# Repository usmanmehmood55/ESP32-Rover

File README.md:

# ESP32 based UGV
Made using PlatformIO and being tested on a custom PCB for my final
year project: 3D Mapping using Stereo Vision. This board, along with
its firmware are simply handle two DC motors, their encoders and two servo motors. 
The motors are driven by DRV8840 chip, for which, a simple and easy to use library 
has been written and included.

MQTT added on June 5th. Receives 10-character commands from Nvidia Jetson TX2 
to operate motors and return distance traveled

Still working on distance calculations, had *some* progress with it, which is included in the latest commit

Contains main cpp file in src folder and DRV8840.h in include folder

Also might contain gluten.

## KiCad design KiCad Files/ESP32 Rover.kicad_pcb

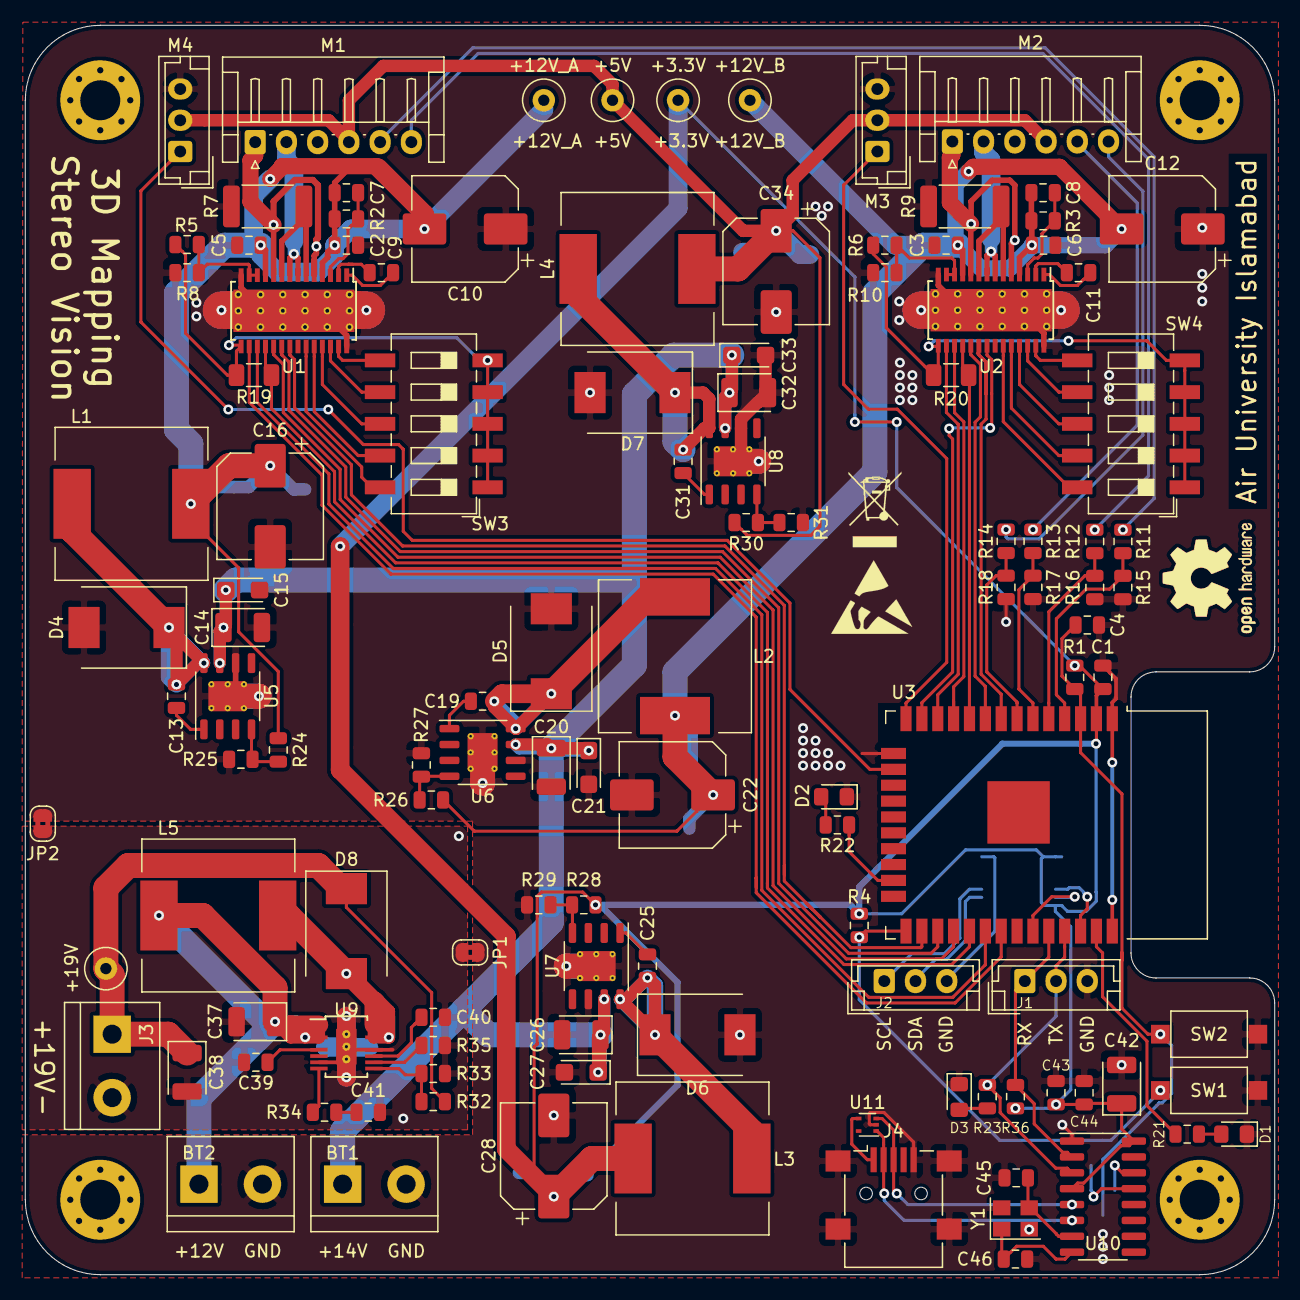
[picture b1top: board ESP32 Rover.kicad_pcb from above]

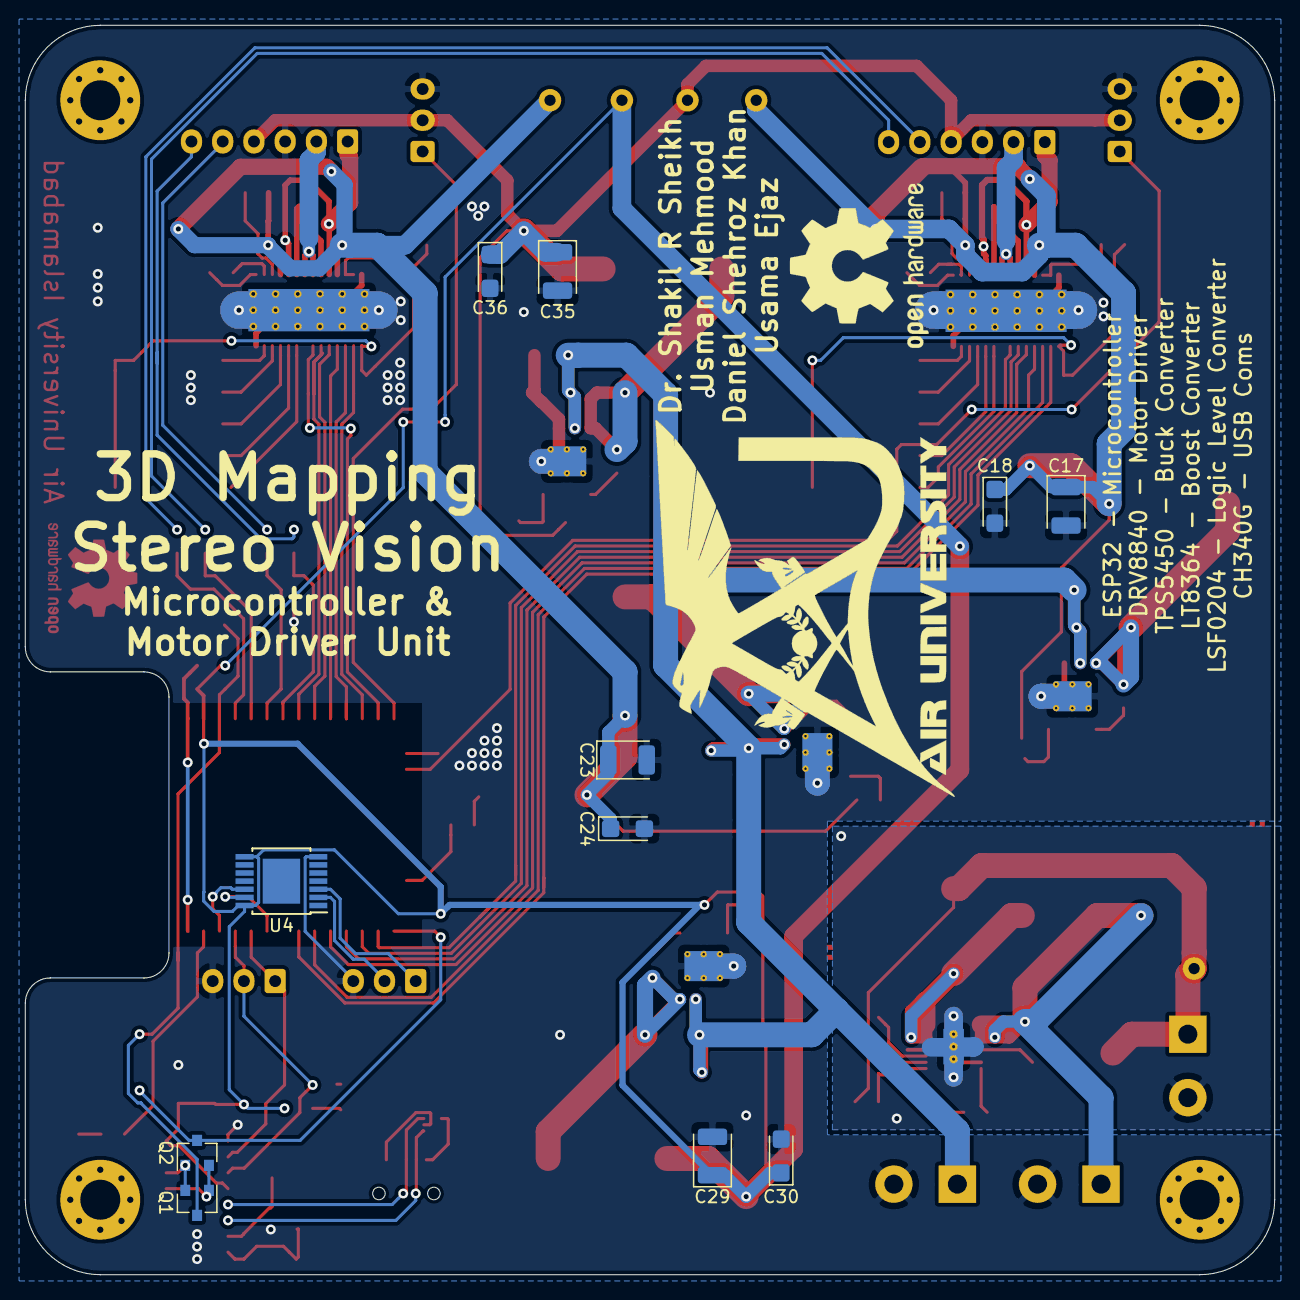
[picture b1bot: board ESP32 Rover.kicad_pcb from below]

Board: 2 copper layers, 100.0 x 100.0 mm, 138 parts (11 on the bottom side), 96 nets.

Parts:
BIN: BIN; WEEE-Logo_4.2x6mm_SilkScreen
BT1: 14.8V; TerminalBlock_bornier-2_P5.08mm
BT2: 11.1V; TerminalBlock_bornier-2_P5.08mm
C1, C39: 1uF; C_0805_2012Metric
C2, C3, C5, C6, C7, C8: 0.1uF; C_0805_2012Metric
C4, C9, C11, C13, C19, C25, C31, C43: 100nF; C_0805_2012Metric
C10, C12: 100uF; CP_Elec_8x10
C14, C17, C20, C23, C26, C29, C32, C35, C37, C38, C42: 4.7uF; CP_EIA-3528-15_AVX-H
C15, C18, C21, C24, C27, C30, C33, C36: 220nF; CP_EIA-3216-18_Kemet-A
C16, C22, C28, C34: 330uF; CP_Elec_8x10
C40, C44: 10nF; C_0805_2012Metric
C41: 2.2nF; C_0805_2012Metric
C45, C46: 22pF; C_0805_2012Metric
D1, D2, D3: LED; LED_0805_2012Metric_Pad1.15x1.40mm_HandSolder
D4, D5, D6, D7, D8: 5A; D_SMC
ESD: ESD; ESD-Logo_6.6x6mm_SilkScreen
H1, H2, H3, H4: MH; MountingHole_3.2mm_M3_Pad_Via
J1: UART; JST_EH_B3B-EH-A_1x03_P2.50mm_Vertical
J2: i2c_jetson; JST_EH_B3B-EH-A_1x03_P2.50mm_Vertical
J3: T-Block; TerminalBlock_bornier-2_P5.08mm
J4: USB_B_Mini; USB_Mini-B_Lumberg_2486_01_Horizontal
JP1, JP2: SolderJumper_2_Bridged; SolderJumper-2_P1.3mm_Bridged2Bar_RoundedPad1.0x1.5mm
L1, L2, L3, L4: 15uH; L_Pulse_PA4320
L5: 2.4uH; L_Pulse_PA4320
M1, M2: PL37D; JST_EH_S6B-EH_1x06_P2.50mm_Horizontal
M3, M4: Servo; JST_EH_B3B-EH-A_1x03_P2.50mm_Vertical
OSHW: OSHW; OSHW-Logo2_9.8x8mm_SilkScreen
OSHW#2: OSHW; OSHW-Logo2_9.8x8mm_Copper
Q1, Q2: BSS138; SOT-23
R1, R4, R5, R6, R24, R25, R26, R27, R28, R29, R30, R31: 10K; R_0805_2012Metric
R2, R3: 1M; R_0805_2012Metric
R7, R9: 0.1R; R_2512_6332Metric
R8, R10: 31K; R_0805_2012Metric
R11, R12, R13, R14: 1K; R_0805_2012Metric
R15, R16, R17, R18: 2K; R_0805_2012Metric
R19, R20: 10K; R_1206_3216Metric
R21, R22, R23: 83; R_0805_2012Metric
R32: 10k; R_0805_2012Metric
R33: 100k; R_0805_2012Metric
R34: 36.5k; R_0805_2012Metric
R35: 20k; R_0805_2012Metric
R36: 4.7K; R_0805_2012Metric
SW1: BOOT/FLASH; SW_SPST_CK_RS282G05A3
SW2: RESET; SW_SPST_CK_RS282G05A3
SW3, SW4: iChop; SW_DIP_SPSTx05_Slide_6.7x14.26mm_W8.61mm_P2.54mm_LowProfile
TP1: +12V_A; TestPoint_Loop_D2.60mm_Drill0.9mm_Beaded
TP2: +12V_B; TestPoint_Loop_D2.60mm_Drill0.9mm_Beaded
TP3: +3.3V; TestPoint_Loop_D2.60mm_Drill0.9mm_Beaded
TP4: +5V; TestPoint_Loop_D2.60mm_Drill0.9mm_Beaded
TP5: +19V; TestPoint_Loop_D2.60mm_Drill0.9mm_Beaded
U1, U2: DRV8840; HTSSOP-28-1EP_4.4x9.7mm_P0.65mm_EP3.4x9.5mm_Mask2.4x6.17mm_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
U3: ESP32-WROOM-32D; ESP32-WROOM-32
U4: LSF0204; TSSOP-14-1EP_4.4x5mm_P0.65mm
U5, U6, U7, U8: TPS5450; HSOP-8-1EP_3.9x4.9mm_P1.27mm_EP2.41x3.1mm_ThermalVias
U9: LT8364; MSOP-12-16-1EP_3x4mm_P0.5mm_EP1.65x2.85mm_ThermalVias
U10: CH340G; SOIC-16_3.9x9.9mm_P1.27mm
U11: ESDA6V8AV5; SOT-553
Y1: 12MHz; Crystal_SMD_3225-4Pin_3.2x2.5mm

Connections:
3P3_1: R5.1, R19.1, SW3.1, SW3.2, SW3.3, SW3.4, SW3.5, U1.15
3P3_2: R6.1, R20.1, SW4.1, SW4.2, SW4.3, SW4.4, SW4.5, U2.15
+3V3: C1.1, C28.1, C29.1, C30.1, C42.1, C43.1, C44.1, L3.2, R1.1, R4.1, R28.1, R36.1, TP3.1, U3.2, U4.8, U4.14, U10.4, U10.16
+5V: C34.1, C35.1, C36.1, L4.2, M1.4, M2.4, M3.2, M4.2, R30.1, TP4.1
+12V: BT2.1, C37.1, L5.1, U9.1, U9.3
/M1+: M1.1, U1.5, U1.10
/M1-: M1.2, U1.7, U1.8
/M2+: M2.1, U2.5, U2.10
/M2-: M2.2, U2.7, U2.8
BOOT: Q2.3, R4.2, SW1.1, U3.25
D+: J4.3, U10.5, U11.3
D-: J4.2, U10.6, U11.1
DTR: Q1.1, Q2.2, U10.13
EC1A: R11.2, R15.1, U3.4
EC1B: R12.2, R16.1, U3.5
EC2A: R13.2, R17.1, U3.6
EC2B: R14.2, R18.1, U3.7
EN: C4.1, Q1.3, R1.2, SW2.1, U3.3
ENC1A: M1.5, R11.1
ENC1B: M1.6, R12.1
ENC2A: M2.5, R13.1
ENC2B: M2.6, R14.1
GND: BT1.2, BT2.2, C1.2, C2.1, C3.1, C4.2, C5.1, C6.1, C10.1, C12.1, C14.2, C15.2, C16.2, C17.2, C18.2, C20.2, C21.2, C22.2, C23.2, C24.2, C26.2, C27.2, C28.2, C29.2, C30.2, C32.2, C33.2, C34.2, C35.2, C36.2, C42.2, C43.2, C44.2, C45.2, C46.2, D1.1, D2.1, D3.1, D4.2, D5.2, D6.2, D7.2, J1.3, J2.3, J4.5, J4.6, JP1.1, JP2.1, M1.3, M2.3, M3.3, M4.3, R7.2, R8.2, R9.2, R10.2, R15.2, R16.2, R17.2, R18.2, R25.2, R27.2, R29.2, R31.2, SW1.2, SW2.2, U1.14, U1.28, U1.29, U2.14, U2.28, U2.29, U3.1, U3.15, U3.38, U4.7, U5.6, U5.9, U6.6, U6.9, U7.6, U7.9, U8.6, U8.9, U10.1, U11.2, Y1.2, Y1.4
GNDD: C37.2, C38.2, C39.2, C40.2, C41.2, J3.2, JP1.2, JP2.2, R33.2, R35.1, U9.7, U9.12, U9.17
M1C0: SW3.10, U1.23
M1C1: SW3.9, U1.24
M1C2: SW3.8, U1.25
M1C3: SW3.7, U1.26
M1C4: SW3.6, U1.27
M1DECAY: U1.19, U3.28
M1FAULT: R19.2, U1.18, U3.29
M1PHASE: U1.20, U3.27
M1PWM: U1.21, U3.26
M1RST: U1.16, U3.31
M1SLEEP: U1.17, U3.30
M2C0: SW4.10, U2.23
M2C1: SW4.9, U2.24
M2C2: SW4.8, U2.25
M2C3: SW4.7, U2.26
M2C4: SW4.6, U2.27
M2DECAY: U2.19, U3.9
M2FAULT: R20.2, U2.18, U3.10
M2PHASE: U2.20, U3.8
M2PWM: U2.21, U3.13
M2RST: U2.16, U3.12
M2SLEEP: U2.17, U3.11
unnamed: C7.2, R2.2, U1.3
unnamed: C8.2, R3.2, U2.3
unnamed: C9.1, U1.1
unnamed: C9.2, U1.2
unnamed: C11.1, U2.1
unnamed: C11.2, U2.2
unnamed: C13.1, D4.1, L1.1, U5.8
unnamed: C13.2, U5.1
unnamed: C19.1, D5.1, L2.1, U6.8
unnamed: C19.2, U6.1
unnamed: C25.1, D6.1, L3.1, U7.8
unnamed: C25.2, U7.1
unnamed: C31.1, D7.1, L4.1, U8.8
unnamed: C31.2, U8.1
unnamed: C39.1, U9.5
unnamed: C40.1, U9.11
unnamed: C41.1, R34.2
unnamed: D1.2, R21.2
unnamed: D2.2, R22.2
unnamed: D3.2, R23.2
unnamed: D8.2, L5.2, U9.14, U9.16
unnamed: R5.2, R8.1, U1.12, U1.13
unnamed: R7.1, U1.6, U1.9
unnamed: R9.1, U2.6, U2.9
unnamed: R6.2, R10.1, U2.12, U2.13
unnamed: R32.2, R33.1, U9.9
unnamed: R34.1, U9.8
unnamed: R35.2, U9.10
O1: C45.1, U10.7, Y1.3
O2: C46.1, U10.8, Y1.1
RTS: Q1.2, Q2.1, U10.14
RX: J1.1, R36.2, U3.34, U10.2
SCL: U3.36, U4.12
SCL1: J2.1, U4.3
SDA: U3.33, U4.13
SDA1: J2.2, U4.2
SRV1: M3.1, U3.14
SRV2: M4.1, U3.16
STAT1: R21.1, U3.37
STAT2: R22.1, U3.23
TX: J1.2, R23.1, U3.35, U10.3
VBUS: J4.1, U11.4
VDC: BT1.1, C14.1, C15.1, C20.1, C21.1, C26.1, C27.1, C32.1, C33.1, U5.7, U6.7, U7.7, U8.7
VSNS1: R24.2, R25.1, U5.4
VSNS2: R26.2, R27.1, U6.4
VSNS3: R28.2, R29.1, U7.4
VSNS4: R30.2, R31.1, U8.4
V_SoC: C38.1, D8.1, J3.1, R32.1, TP5.1
vMotor1: C2.2, C5.2, C7.1, C10.2, C16.1, C17.1, C18.1, L1.2, R2.1, R24.1, TP1.1, U1.4, U1.11
vMotor2: C3.2, C6.2, C8.1, C12.2, C22.1, C23.1, C24.1, L2.2, R3.1, R26.1, TP2.1, U2.4, U2.11

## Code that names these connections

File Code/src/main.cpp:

#include <Arduino.h>
#include <DRV8840.h>

// Motor Driver IN
unsigned const char M1RST = 19;
unsigned const char M1PWM = 04;
unsigned const char M1PHASE = 16;
unsigned const char M1SLEEP = 18;
unsigned const char M1DECAY = 17;
unsigned const char M2RST = 27;
unsigned const char M2PWM = 14;
unsigned const char M2PHASE = 32;
unsigned const char M2SLEEP = 26;
unsigned const char M2DECAY = 33;

//Motor Driver OUT
unsigned const char ENCODER_1A = 36;
unsigned const char ENCODER_1B = 39;
unsigned const char ENCODER_2A = 34;
unsigned const char ENCODER_2B = 35;
unsigned const char M1FAULT = 05;
unsigned const char M2FAULT = 25;

// PWM
unsigned const char PWMchannel_0 = 0;
unsigned const char PWMchannel_1 = 1;
unsigned const int freq = 5000;
unsigned const char resolution = 8;

DRV8840 M1(
    M1PWM,
    PWMchannel_0,
    M1PHASE,
    M1DECAY,
    M1SLEEP,
    M1RST,
    ENCODER_1A,
    ENCODER_1B);

DRV8840 M2(
    M2PWM,
    PWMchannel_1,
    M2PHASE,
    M2DECAY,
    M2SLEEP,
    M2RST,
    ENCODER_2A,
    ENCODER_2B);

int distance1 = 0;
int distance2 = 0;

void encoderRead1();
void encoderRead2();

void setup()
{
  Serial.begin(115200);

  pinMode(M1FAULT, INPUT);
  pinMode(M2FAULT, INPUT);
  attachInterrupt(digitalPinToInterrupt(ENCODER_1B), encoderRead1, CHANGE);
  attachInterrupt(digitalPinToInterrupt(ENCODER_2B), encoderRead2, CHANGE);

  // PWM Setup
  ledcSetup(PWMchannel_0, freq, resolution);
  ledcAttachPin(M1PWM, PWMchannel_0);
  ledcSetup(PWMchannel_1, freq, resolution);
  ledcAttachPin(M2PWM, PWMchannel_1);

  M1.getData();
  M2.getData();
  Serial.println();
  Serial.println("Setup Complete!");
}

void loop()
{
  M1.motorForward(255); 
  Serial.print(M1.getDistance());
  Serial.print("    ");
  M2.motorForward(255); 
  Serial.print(M1.getDistance());
  Serial.println();
}

// Use if ISR inside DRV8840.h does not run
void IRAM_ATTR encoderRead1()
{
  M1.encoderRead();
}

void IRAM_ATTR encoderRead2()
{
  M2.encoderRead();
}

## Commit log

2020-03-08 Remove duplicated directory
2020-03-08 Linked to Git
2020-03-08 Files Updated
2020-03-08 Repairs lol
2020-03-08 Readme added
2020-03-08 Readme. Again
2020-03-08 Readme
2020-03-08 Started getCoordinates()
2020-03-08 getCoordinates
2020-03-08 Removed useless comment
2020-03-08 Re-commit
2020-03-08 Distance calculations
2020-06-05 MQTT configured and integrated
2020-06-05 Motor functions altered
2020-06-06 Adjustments
2020-06-06 incoming message demux
2020-06-06 motorBehaviour function added
2020-06-06 working on hardware
2020-06-06 callback issues resolved
2020-06-06 callback issue resolved
2020-06-06 readme updated
2020-06-20 Alpha Release
2020-06-30 Create LICENSE
2020-07-11 encoder code ongoing
2020-07-11 getCoordinates ( ) updated
